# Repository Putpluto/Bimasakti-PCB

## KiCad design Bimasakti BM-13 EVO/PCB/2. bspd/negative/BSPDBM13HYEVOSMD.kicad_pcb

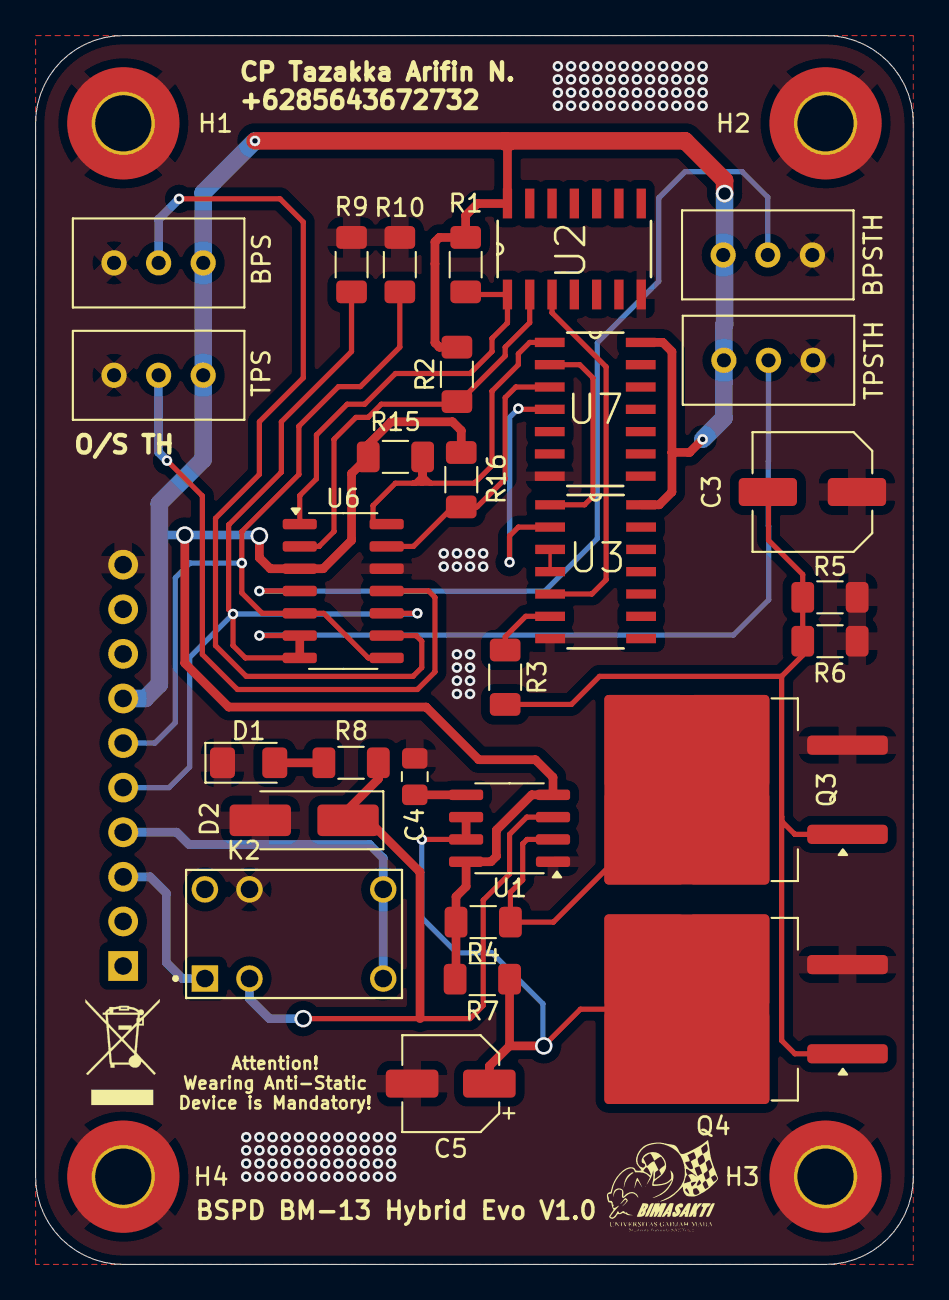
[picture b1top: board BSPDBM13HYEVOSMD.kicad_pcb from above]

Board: 2 copper layers, 50.0 x 70.0 mm, 34 parts (1 on the bottom side), 24 nets.

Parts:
BPS: R_Potentiometer_Trim; Potentiometer_Bourns_3296W_Vertical
BPSTH: R_Potentiometer_Trim; Potentiometer_Bourns_3296W_Vertical
C3: 100uF; C_Elec_6.3x7.7
C4: 1uF; C_0805_2012Metric_Pad1.18x1.45mm_HandSolder
C5: 10uF; CP_Elec_5x5.3
D1: LED; LED_1206_3216Metric_Pad1.42x1.75mm_HandSolder
D2: SS210; D_SMA_Handsoldering
H1, H2, H3, H4: MountingHole_Pad; MountingHole_3.2mm_M3_Pad_TopBottom
J1: Conn_01x10_Pin; PinHeader_1x10_P2.54mm_Vertical
K2: G5V-1_DC5; RELAY_G5V-1_DC5
Q3, Q4: IRFS4127; TO-263-2
R1, R2, R3, R4, R15, R16: 10K; R_1206_3216Metric_Pad1.30x1.75mm_HandSolder
R5, R6: 100K; R_1206_3216Metric_Pad1.30x1.75mm_HandSolder
R7, R9, R10: 1M; R_1206_3216Metric_Pad1.30x1.75mm_HandSolder
R8: 150; R_1206_3216Metric_Pad1.30x1.75mm_HandSolder
TPS: R_Potentiometer_Trim; Potentiometer_Bourns_3296W_Vertical
TPSTH: R_Potentiometer_Trim; Potentiometer_Bourns_3296W_Vertical
U1: NE555D; SOIC-8_3.9x4.9mm_P1.27mm
U2: 74HC08D-T; SOIC127P600X175-14N
U3: 74HC32D_653; SOIC127P600X175-14N
U6: LM339; SOIC-14_3.9x8.7mm_P1.27mm
U7: 74HC04D; SOIC127P600X175-14N

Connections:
+5V: BPS.1, BPSTH.1, J1.7, R1.1, R2.2, R4.2, R7.2, R15.1, R16.1, TPS.1, TPSTH.1, U1.4 (R), U1.8 (VCC), U2.14 (VCC), U3.14 (VCC), U6.3 (V+), U7.14 (VCC)
BrakePress: J1.6, R10.2, U6.5 (+), U6.8 (-)
COM: J1.4, K2.5, K2.6
GND: BPS.3, BPSTH.3, C3.1, C4.2, C5.2, D1.1 (K), D2.2 (A), H1.1, H2.1, H3.1, H4.1, J1.10, K2.9, Q3.3 (S), Q4.3 (S), R5.1, R6.1, R9.1, R10.1, TPS.3, TPSTH.3, U1.1 (GND), U2.7 (GND), U3.7 (GND), U6.12 (V-), U7.7 (GND)
NC: J1.3, K2.1
unnamed: D1.2 (A), R8.1
unnamed: D2.1 (K), K2.2, R8.2, U1.3 (Q)
unnamed: Q3.2 (D), R4.1, U1.2 (TR)
unnamed: C3.2, Q3.1 (G), Q4.1 (G), R3.2, R5.2, R6.2
unnamed: C5.1, Q4.2 (D), R7.1, U1.6 (THR), U1.7 (DIS)
unnamed: C4.1, U1.5 (CV)
unnamed: R1.2, U2.1 (1A), U6.1
unnamed: R2.1, U2.2 (1B), U6.2
unnamed: U2.3 (1Y), U3.5 (2B)
unnamed: U3.1 (1A), U7.2 (1Y)
unnamed: U3.2 (1B), U7.4 (2Y)
unnamed: U3.3 (1Y), U3.4 (2A)
unnamed: R3.1, U3.6 (2Y)
unnamed: BPSTH.2, U6.4 (-)
unnamed: TPS.2, U6.11 (+)
unnamed: BPS.2, U6.9 (+)
unnamed: R15.2, U6.14, U7.1 (1A)
unnamed: R16.2, U6.13, U7.3 (2A)
ThrottlePos: J1.5, R9.2, TPSTH.2, U6.6 (-), U6.7 (+), U6.10 (-)

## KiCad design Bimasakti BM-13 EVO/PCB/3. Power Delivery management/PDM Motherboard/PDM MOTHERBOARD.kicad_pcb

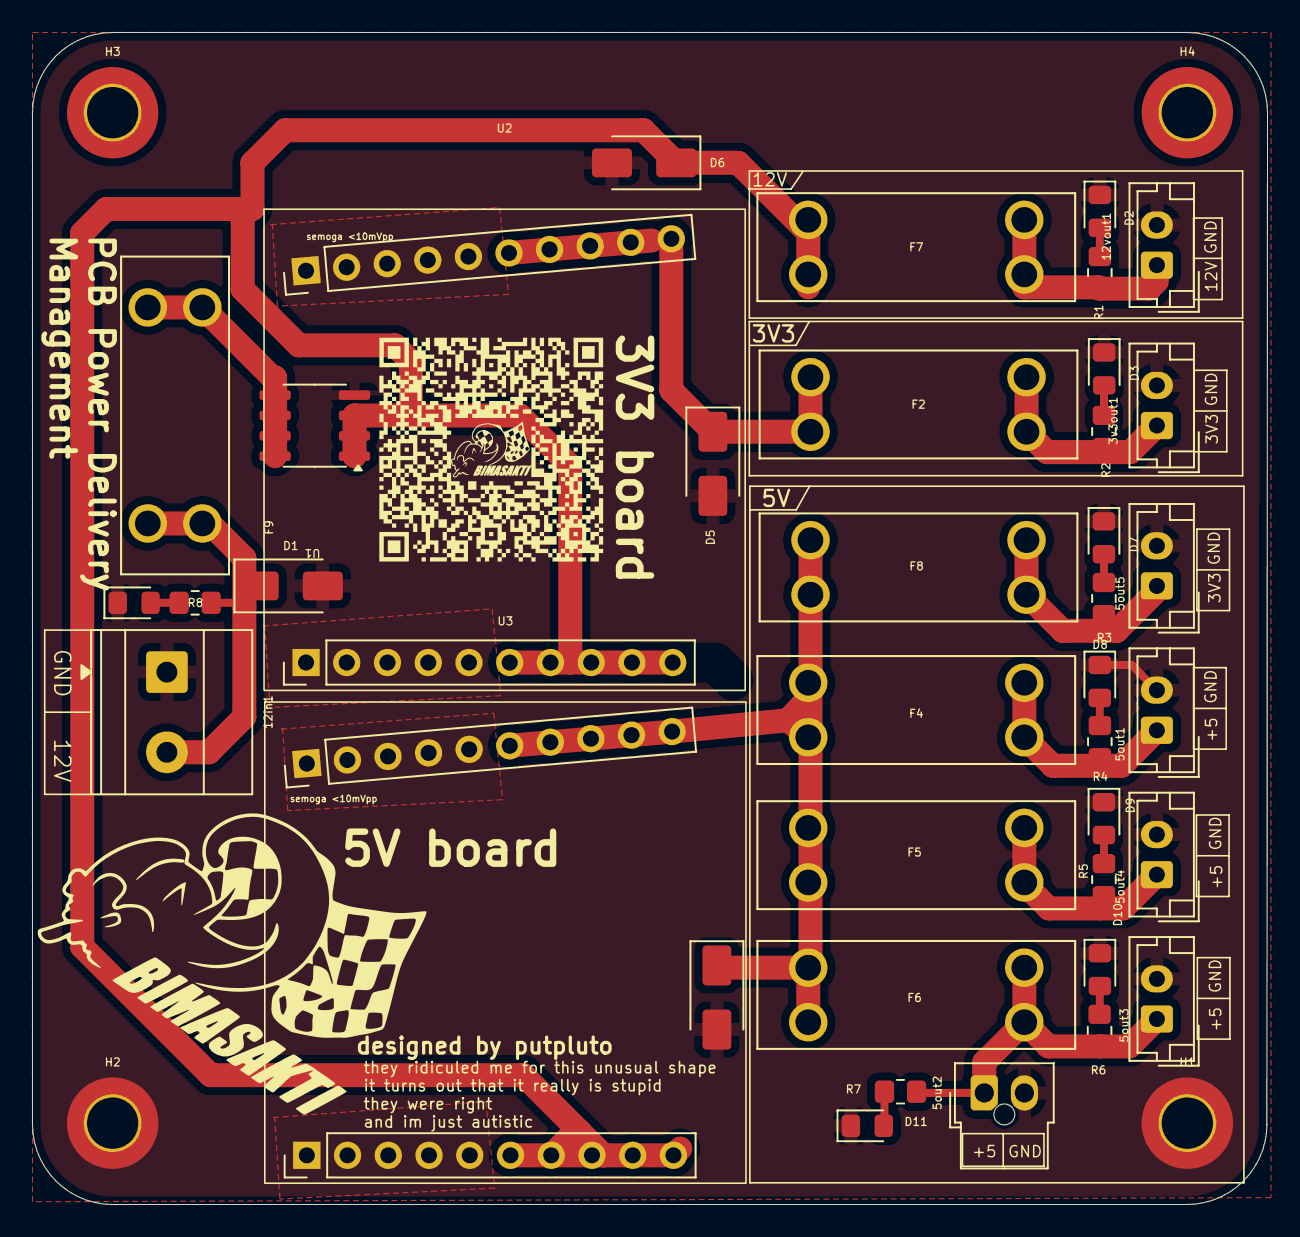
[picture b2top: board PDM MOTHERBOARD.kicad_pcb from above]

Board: 2 copper layers, 77.0 x 73.1 mm, 42 parts (0 on the bottom side), 20 nets.

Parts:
3v3out1, 5out1, 5out3, 5out4, 5out5, 12vout1: JST_EH_B2B-EH-A_1x02_P2.50mm_Vertical
5out2: Molex_Nano-Fit_105309-xx02_1x02_P2.50mm_Vertical
12in1: TerminalBlock_Phoenix_MKDS-1,5-2_1x02_P5.00mm_Horizontal
D1: SMAJ24A; D_SMA
D2, D3, D7, D8, D9, D10, D11, D12: LED; LED_0805_2012Metric_Pad1.15x1.40mm_HandSolder
D4, D5, D6: SMAJ5.0A; D_SMA
F2, F4, F5, F6, F7, F8, F9: 3557-2; 0_FUSE_3557-2
H1, H2, H3, H4: MountingHole_Pad; MountingHole_3.2mm_M3_ISO7380_Pad_TopBottom
R1, R8: 1k; R_0805_2012Metric_Pad1.20x1.40mm_HandSolder
R2, R3: 220R; R_0805_2012Metric_Pad1.20x1.40mm_HandSolder
R4, R5, R6, R7: 330R; R_0805_2012Metric_Pad1.20x1.40mm_HandSolder
U1: SOIC-8 (AOD)
U2, U3: BIMS_BUCK

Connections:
3Vin: D5.1 (A1), F2.1_1, F2.1_2, U2.16 (3V3), U2.17 (3V3), U2.18 (3V3), U2.19 (3V3), U2.20 (3V3)
5Vin: D4.1 (A1), F4.1_1, F4.1_2, F5.1_1, F5.1_2, F6.1_1, F6.1_2, F8.1_1, F8.1_2, U3.16 (5V), U3.17 (5V), U3.18 (5V), U3.19 (5V), U3.20 (5V)
12tobuck: D6.1 (A1), F7.1_1, F7.1_2, U1.3 (S), U2.6 (12VIN), U2.7 (12VIN), U2.8 (12VIN), U2.9 (12VIN), U2.10 (12VIN), U3.6 (12VIN), U3.7 (12VIN), U3.8 (12VIN), U3.9 (12VIN), U3.10 (12VIN)
/5v_f3: 5out2.1, 5out3.1, F6.2_1, F6.2_2, R6.1, R7.1
GND: 3v3out1.2, 5out1.2, 5out2.2, 5out3.2, 5out4.2, 5out5.2, 12in1.1, 12vout1.2, D1.2 (A2), D2.1 (K), D3.1 (K), D4.2 (A2), D5.2 (A2), D6.2 (A2), D7.1 (K), D8.1 (K), D9.1 (K), D10.1 (K), D11.1 (K), D12.1 (K), H1.1, H2.1, U1.2 (G), U2.1 (GND), U2.2 (GND), U2.3 (GND), U2.4 (GND), U2.5 (GND), U2.11 (GND), U2.12 (GND), U2.13 (GND), U2.14 (GND), U2.15 (GND), U3.1 (GND), U3.2 (GND), U3.3 (GND), U3.4 (GND), U3.5 (GND), U3.11 (GND), U3.12 (GND), U3.13 (GND), U3.14 (GND), U3.15 (GND)
unnamed: 3v3out1.1, F2.2_1, F2.2_2, R2.1
unnamed: 5out1.1, F4.2_1, F4.2_2, R4.1
unnamed: 5out4.1, F5.2_1, F5.2_2, R5.1
unnamed: 5out5.1, F8.2_1, F8.2_2, R3.1
unnamed: 12in1.2, D1.1 (A1), F9.1_1, F9.1_2, R8.1
unnamed: 12vout1.1, F7.2_1, F7.2_2, R1.1
unnamed: D2.2 (A), R1.2
unnamed: D3.2 (A), R2.2
unnamed: D7.2 (A), R3.2
unnamed: D8.2 (A), R4.2
unnamed: D9.2 (A), R5.2
unnamed: D10.2 (A), R6.2
unnamed: D11.2 (A), R7.2
unnamed: D12.2 (A), R8.2
unnamed: F9.2_1, F9.2_2, U1.1 (D)

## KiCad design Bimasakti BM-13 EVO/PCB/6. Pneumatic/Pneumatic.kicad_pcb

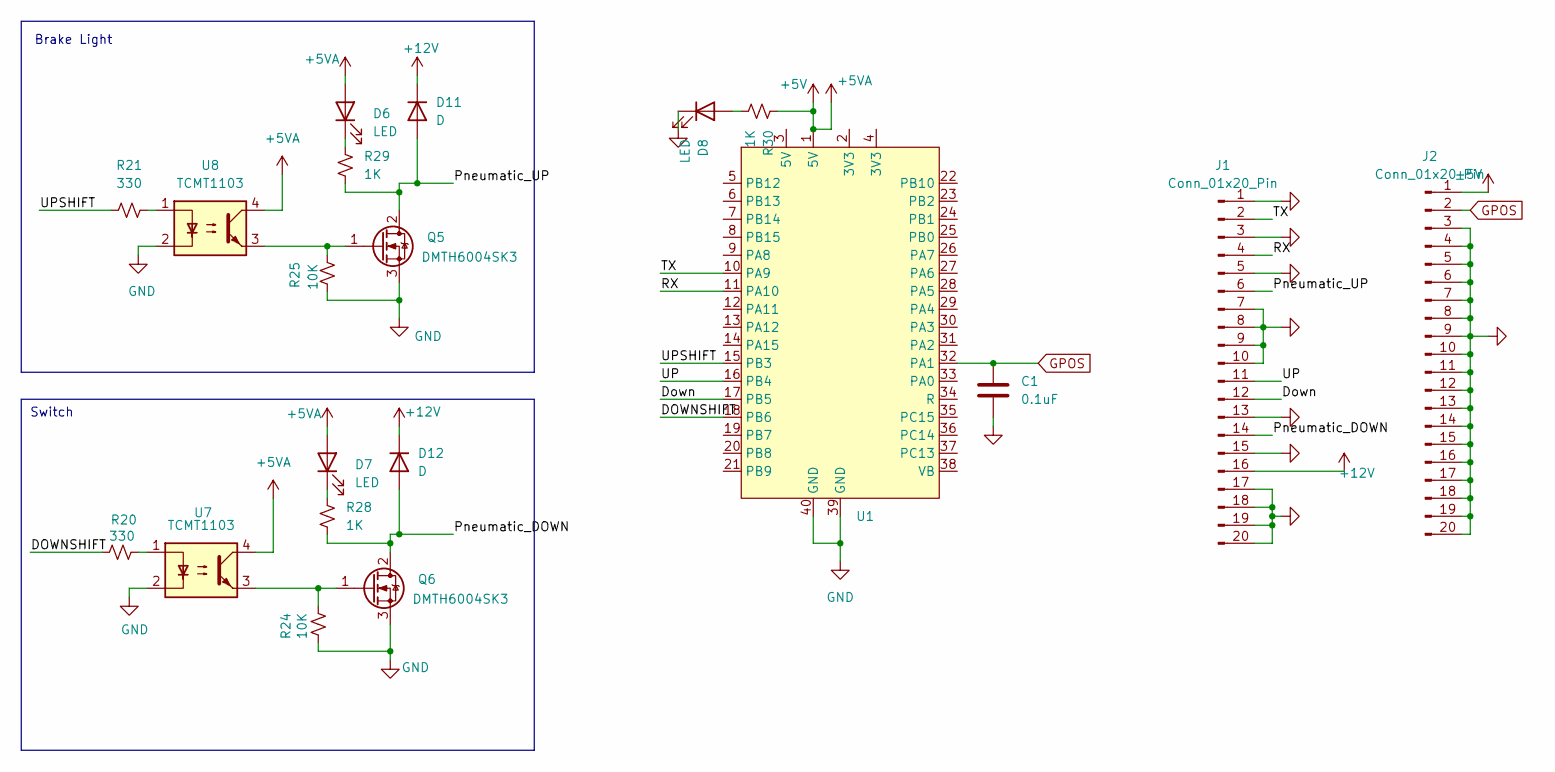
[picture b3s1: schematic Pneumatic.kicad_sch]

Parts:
C1: 0.1uF; C_0603_1608Metric_Pad1.08x0.95mm_HandSolder
D6, D7, D8: LED; LED_0603_1608Metric_Pad1.05x0.95mm_HandSolder
D11, D12: D; D_0603_1608Metric_Pad1.05x0.95mm_HandSolder
J1, J2: Conn_01x20_Pin; PinHeader_1x20_P2.54mm_Vertical
Q5, Q6: DMTH6004SK3; TO-252-2
R20, R21: 330; R_0603_1608Metric_Pad0.98x0.95mm_HandSolder
R24, R25: 10K; R_0603_1608Metric_Pad0.98x0.95mm_HandSolder
R28, R29, R30: 1K; R_0603_1608Metric_Pad0.98x0.95mm_HandSolder
U1: Blackpill PLT
U7, U8: TCMT1103; SOP-4_4.4x2.6mm_P1.27mm

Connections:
+5V: D6.2 (A), D7.2 (A), J2.1, R30.1, U1.1 (5V), U7.4, U8.4
+12V: D11.1 (K), D12.1 (K), J1.16
/DOWNSHIFT: R20.1, U1.18 (PB6)
/Down: J1.12, U1.17 (PB5)
/Pneumatic_DOWN: D12.2 (A), J1.14, Q6.2 (D), R28.2
/Pneumatic_UP: D11.2 (A), J1.6, Q5.2 (D), R29.2
/RX: J1.4, U1.11 (PA10)
/TX: J1.2, U1.10 (PA9)
/UP: J1.11, U1.16 (PB4)
/UPSHIFT: R21.1, U1.15 (PB3)
GND: C1.1, D8.1 (K), J1.1, J1.3, J1.5, J1.7, J1.8, J1.9, J1.10, J1.13, J1.15, J1.17, J1.18, J1.19, J1.20, J2.3, J2.4, J2.5, J2.6, J2.7, J2.8, J2.9, J2.10, J2.11, J2.12, J2.13, J2.14, J2.15, J2.16, J2.17, J2.18, J2.19, J2.20, Q5.3 (S), Q6.3 (S), R24.1, R25.1, U1.39 (GND), U1.40 (GND), U7.2, U8.2
GPOS: C1.2, J2.2, U1.32 (PA1)
unnamed: D6.1 (K), R29.1
unnamed: D7.1 (K), R28.1
unnamed: D8.2 (A), R30.2
unnamed: Q5.1 (G), R25.2, U8.3
unnamed: Q6.1 (G), R24.2, U7.3
unnamed: R20.2, U7.1
unnamed: R21.2, U8.1

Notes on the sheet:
Brake Light
Switch

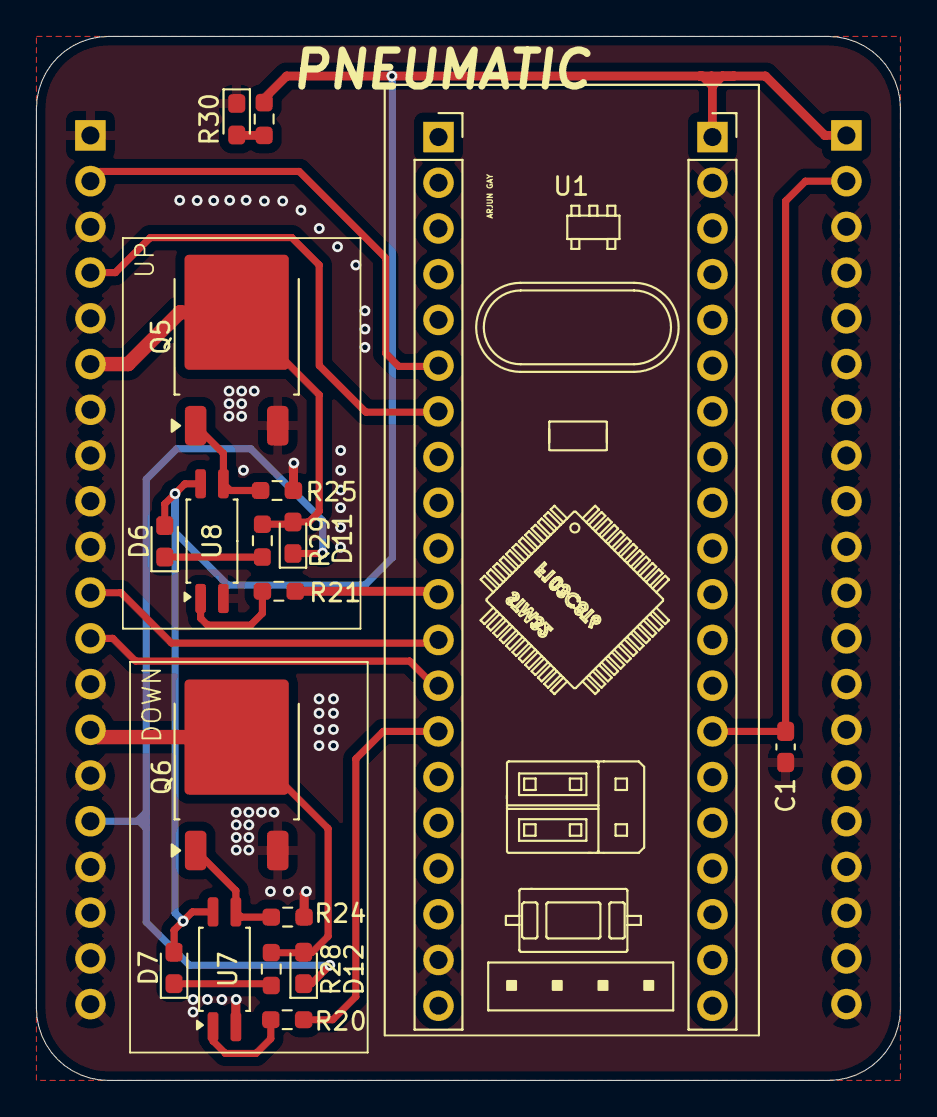
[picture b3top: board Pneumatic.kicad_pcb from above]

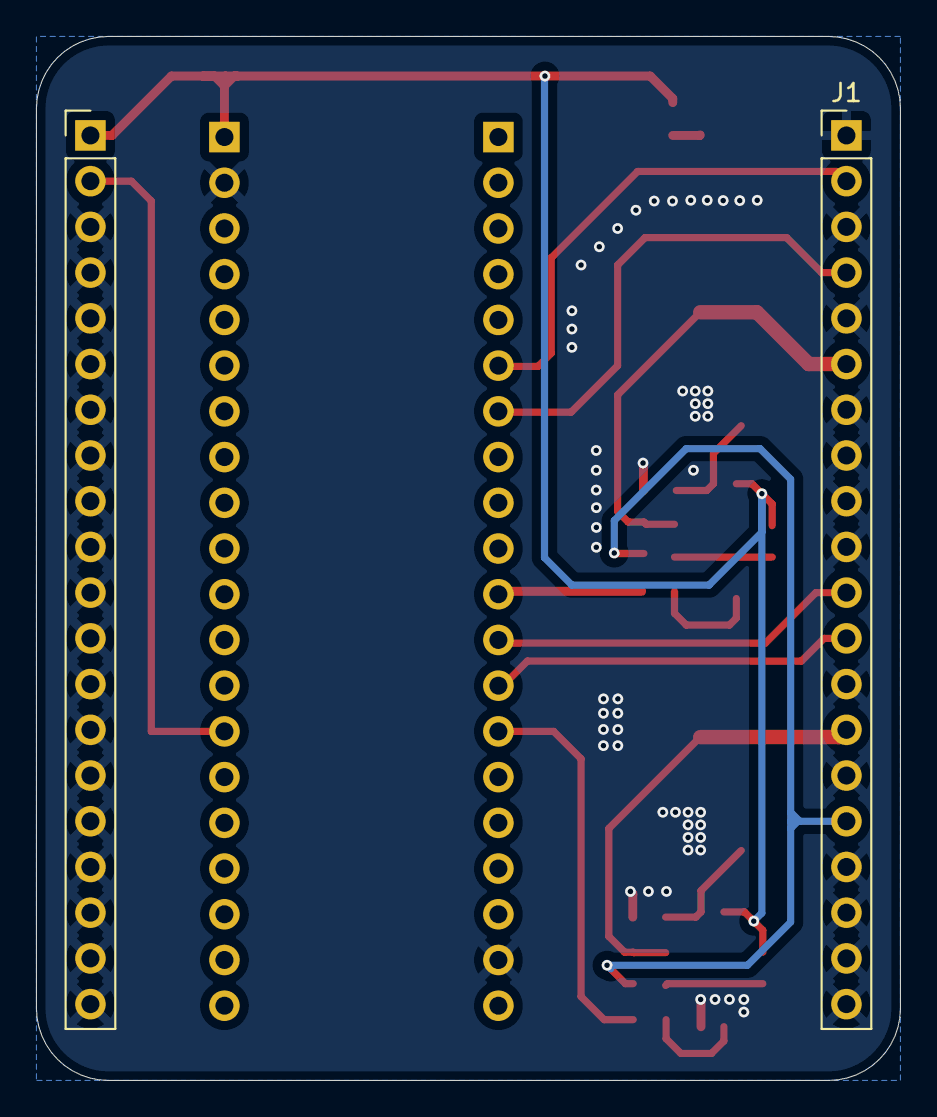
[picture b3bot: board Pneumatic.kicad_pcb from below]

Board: 2 copper layers, 48.0 x 58.0 mm, 20 parts (2 on the bottom side), 19 nets.

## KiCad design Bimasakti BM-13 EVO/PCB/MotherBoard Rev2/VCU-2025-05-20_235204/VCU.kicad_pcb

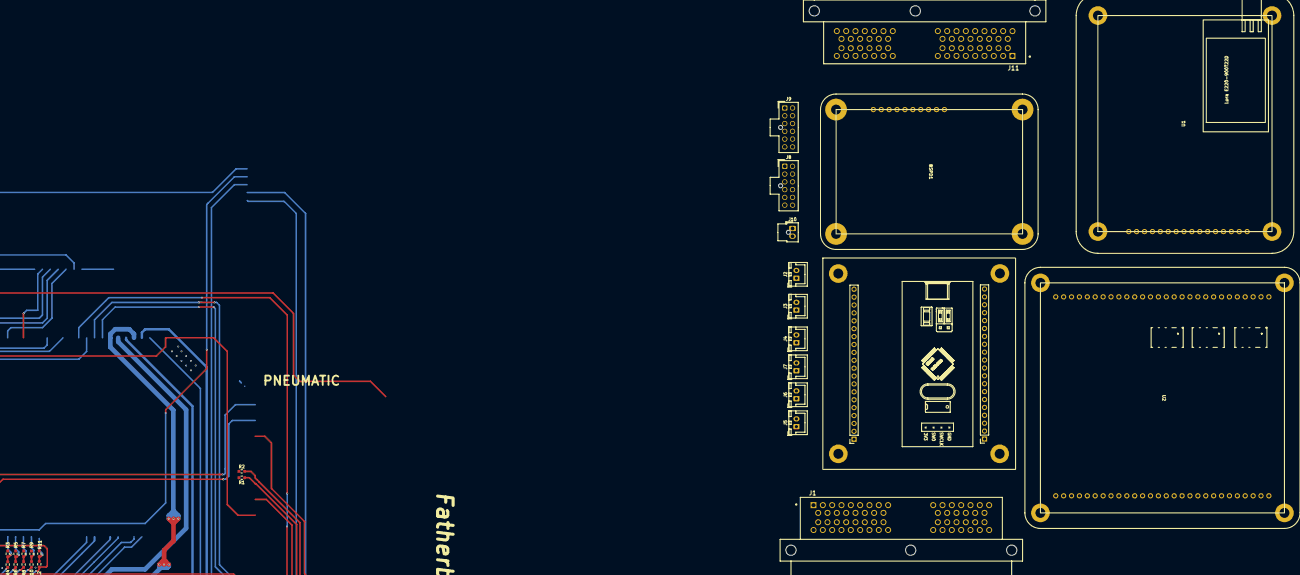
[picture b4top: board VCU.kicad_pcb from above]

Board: 2 copper layers, 27 parts (0 on the bottom side), 57 nets.

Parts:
BSPD1: FootPrintBPSD
J1, J11: 6437288-3; VCU_CONNECTOR_TE_6437288-3
J2: 12V; JST_XH_B2B-XH-A_1x02_P2.50mm_Vertical
J3: 3V3_1; JST_XH_B2B-XH-A_1x02_P2.50mm_Vertical
J4: 5V_5; JST_XH_B2B-XH-A_1x02_P2.50mm_Vertical
J5: 5V_1; JST_XH_B2B-XH-A_1x02_P2.50mm_Vertical
J6: 5V_2; JST_XH_B2B-XH-A_1x02_P2.50mm_Vertical
J7: 5V_3; JST_XH_B2B-XH-A_1x02_P2.50mm_Vertical
J8: SIGNAL 1; Molex_Nano-Fit_105310-xx12_2x06_P2.50mm_Vertical
J9: SIGNAL 2; Molex_Nano-Fit_105310-xx12_2x06_P2.50mm_Vertical
J10: power; Molex_Nano-Fit_105309-xx02_1x02_P2.50mm_Vertical
R1, R2: R; R_0603_1608Metric_Pad0.98x0.95mm_HandSolder
R3, R5, R7, R9, R11: 2K; R_0603_1608Metric_Pad0.98x0.95mm_HandSolder
R4, R6, R8, R10, R12: 3K; R_0603_1608Metric_Pad0.98x0.95mm_HandSolder
U1: 0_FootprintTelemetry
U2: FootprintVCU
U3: Fooprint Pneumatic

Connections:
5V_B: BSPD1.7 (+5V), J6.1
5V_P: J4.1, U3.9 (5V_IN)
5V_T: J5.1, U1.6 (+5V)
5V_V: J7.1, U2.28 (+5VA)
12V: J2.1, J10.1, U2.1 (+12V), U3.8 (+12V)
AIR: J1.39, U2.7 (AIR)
APPS_IN1: J1.55, J8.12
APPS_IN2: J1.54, J8.11
BMS_HI: J1.36, U2.35 (CANH_1)
BMS_LO: J1.35, U2.36 (CANL_1)
BRAKE_LIGHT: J1.2, U2.11 (Brake_Light)
BRK_P: BSPD1.6 (BrakePress), J1.3, R12.2
BRK_P_L: R11.1, R12.1, U2.45 (Brake_pressure)
COM: BSPD1.4 (COM), J11.9
CS_T: U1.10 (CS2), U2.19 (CS_T)
DISP_HI: J1.42, U2.38 (CANH_3)
DISP_LO: J1.48, U2.39 (CANL_3)
DOWN: J11.36, R1.1, U3.6 (DOWN)
ECU_HI: J1.38, U2.32 (CANH_2)
ECU_LO: J1.37, U2.33 (CANL_2)
ENG_RLY: J11.26, U2.3 (Engine)
ESC1_HI: J1.26, J8.9
ESC1_LO: J1.18, J8.8
ESC2_HI: J1.10, J9.11
ESC2_LO: J1.1, J9.10
FAN_BATT: J11.7, U2.12 (FAN_BATT)
GND: BSPD1.10 (GND), BSPD1.11 (GND), BSPD1.12 (GND), BSPD1.13 (GND), BSPD1.14 (GND), J1.5, J2.2, J3.2, J4.2, J5.2, J6.2, J7.2, J8.7, J10.2, R1.2, R2.1, R3.2, R5.2, R7.2, R9.2, R11.2, U1.1 (GND), U1.2 (GND), U1.3 (GND), U1.4 (GND), U1.5 (GND), U1.11 (GND), U1.12 (GND), U1.13 (GND), U1.14 (GND), U1.15 (GND), U1.16 (GND), U2.2 (GND), U2.13 (GND), U2.15 (GND), U2.17 (GND), U2.18 (GND), U2.20 (GND), U2.22 (GND), U2.24 (GND), U2.26 (GND), U2.30 (GND), U2.31 (GND), U2.34 (GND), U2.37 (GND), U2.40 (GND), U2.41 (GND), U2.50 (GND), U2.53 (GND), U2.56 (GND), U3.1 (GND)
MISO_T: U1.8 (MISO2), U2.23 (MISO_T)
MOSI_T: U1.7 (MOSI2), U2.21 (MOSI_T)
NC: BSPD1.3 (NC), J11.8
PDM: J11.18, U2.4 (PDM)
PNEU_DOWN: J11.35, U3.7 (PENU_DOWN)
PNEU_UP: J11.38, U3.4 (PNEU_UP)
RX_PNEU: U2.51 (RX_PNEU), U3.3 (RX)
SAFETY: J1.40, J1.46, U2.5 (Safety), U2.8 (Safety)
SCK_T: U1.9 (SCK2), U2.25 (SCK_T)
SDC_IN: J11.5, U2.9 (SDC_IN)
SDC_OUT: J11.6, U2.10 (SDC_OUT)
STEER_IN: J1.27, J8.10
STM_RX: J8.6, U2.16 (RX_TV)
STM_TX: J8.5, U2.14 (TX_TV)
SUSP1: J1.6, R4.2
SUSP1_L: R3.1, R4.1, U2.49 (SUS1)
SUSP2: J1.7, R6.2
SUSP2_L: R5.1, R6.1, U2.48 (SUS2)
SUSP3: J1.8, R8.2
SUSP3_L: R7.1, R8.1, U2.47 (SUS3)
SUSP4: J1.9, R10.2
SUSP4_L: R9.1, R10.1, U2.46 (SUS4)
SWITCH_HY: J1.41, U2.6 (Hybrid)
TPS: BSPD1.5 (ThrottlePos), J11.10
TX_PNEU: U2.52 (TX_PNEU), U3.2 (TX)
UP: J11.37, R2.2, U3.5 (UP)
WS_FL: J9.4, J11.3
WS_FR: J9.5, J11.4
WS_RL: J9.2, J11.1
WS_RR: J9.3, J11.2
